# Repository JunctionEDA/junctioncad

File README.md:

<h1 align="center">Junction</h1>

<p align="center"><b>Real-time collaborative KiCad.</b><br>
Schematic and PCB editors where everyone works on the same design at once, on the desktop or in the browser,<br>
with any AI model as a teammate. Open source under GPL-3.0.</p>

<p align="center">
  <a href="https://junctioneda.com"><b>Open in the browser</b></a> ·
  <a href="https://github.com/JunctionEDA/junction/releases/latest"><b>Download for macOS, Windows, Linux</b></a> ·
  <a href="#design-with-an-ai"><b>Connect an AI</b></a>
</p>

<p align="center">

</p>

<!-- The demo video. GitHub plays a video inline only from a github.com/user-attachments URL: to get the inline
     player, drag docs/media/junction-demo.mp4 into this file in GitHub's editor and let the URL it inserts replace
     the poster link below. -->

https://github.com/user-attachments/assets/4089e936-c17c-4153-b253-e5f6324e9056

<p align="center"><sub>Four people build a Raspberry Pi Pico board together, from the first symbol to the filled planes. Music: Grieg, <i>In the Hall of the Mountain King</i>, Musopen (public domain).</sub></p>

## Install

| You want | Do this |
|---|---|
| The browser editor | Open [junctioneda.com](https://junctioneda.com) and sign in with GitHub. Nothing to install. |
| The desktop app | Download Junction for [macOS](https://junctioneda.com/download/macos), [Windows](https://junctioneda.com/download/windows) or [Linux](https://junctioneda.com/download/linux) (newest release; all files on the [releases page](https://github.com/JunctionEDA/junction/releases/latest)). |
| An AI app that designs with you | Add `https://junctioneda.com/mcp` as an MCP server (commands [below](#design-with-an-ai)). |
| Your own server | `cargo run` in [`server/`](server/README.md#running) with a Postgres database. |

Projects are ordinary KiCad files, and projects from any KiCad version from 6 to 10 open as they are. Everyone in a project should be on 2.0: it is built on a much newer KiCad than
1.0.9 and can write things an older client cannot read.

## Quick start

1. In the desktop app choose **File → Online Projects…**, or open the site, and sign in with GitHub.
2. Upload a KiCad project, or start a blank one.
3. **Share…** it with a GitHub username or an email address, or copy an edit, comment-only or view-only link.
4. Open the same schematic or board on both sides. Cursors and edits are live from there.

## What it does

<table>
<tr>
<td width="50%"><br><b>Live, together.</b> Everyone in the same schematic or board, each with their own view. Cursors, selections, drags in progress and edits arrive as they happen, between the desktop app and the browser alike.</td>
<td width="50%"><br><b>The whole board flow.</b> Update PCB from Schematic, placement, interactive routing, zones, DRC and the autorouter, following KiCad's own tools and dialogs.</td>
</tr>
<tr>
<td width="50%"><br><b>Any AI as a teammate.</b> An MCP server lets Claude, ChatGPT, Gemini, Cursor or a local model read and edit your projects. It points at what it means and proposes changes you accept or reject.</td>
<td width="50%"><br><b>GitHub sync.</b> Connect a project to a repository: push, pull and an item-level merge, through a GitHub App installed per repository.</td>
</tr>
<tr>
<td width="50%"><br><b>SPICE in the tab.</b> The simulator runs in the browser, on the schematic you are drawing.</td>
<td width="50%"><br><b>3D and fabrication.</b> The 3D viewer with real part models, and Gerbers, drill, placement and BOM with presets for JLCPCB and PCBWay.</td>
</tr>
</table>

And the rest of what a team needs:

- **Version history.** Every edit of the last 30 days can be scrubbed through; named versions and branches are kept
  for good, and two versions can be compared side by side.
- **Sharing and roles.** Editors, commenters and viewers, by GitHub username, email or link. View links open without
  an account.
- **Review.** Comment threads pinned to parts and nets that follow them when they move.
- **Offline.** The desktop app keeps working without a connection and merges when it returns.
- **Parts.** Search LCSC, Mouser and DigiKey and place the symbol and footprint straight into the schematic.
- **Plugins.** One catalog for built-in, KiCad and community plugins, sandboxed and permissioned.

## Design with an AI

Junction's server is an MCP endpoint. The model is your AI app's: Junction never calls one.

```sh
# Claude Code
claude mcp add --transport http junction https://junctioneda.com/mcp
```

```json
{ "mcpServers": { "junction": { "url": "https://junctioneda.com/mcp" } } }
```

claude.ai, ChatGPT, VS Code, Gemini CLI and Codex are on the site's **Connect an AI assistant** page and in
[server/README.md](server/README.md#mcp-server-any-ai-model-or-service). You sign in once and choose whether it may
make changes; the project's roles apply to it as they do to a person.

Then ask for a board. The model works through a Python harness (`run_python`): one tool call places parts by
name, wires them like the datasheet's application circuit, lays out and routes the board, and returns only what the
script prints, so a design costs few tokens. The Pico board in the video was drawn by
[two such scripts](server/scripts/demo-video/pico) before it was taken apart and put back together on camera.

## Status

Junction 2.2.1 is the current release (the name changed from KiCad Collaborative at 2.0.0). What to know:

- **It is a fork.** Collaboration is built into the editors, so you run Junction's build, not a plugin for stock
  KiCad. It follows upstream KiCad master (merged through 2026-11-17); About says "based on KiCad 10".
- **Same text field, same instant: the later value wins.** There is no merge inside one property. Undo restores
  your version of an item even if a collaborator changed it since.
- **All three desktop builds come from CI**, and each release run installs and launches them on clean machines
  before publishing. Windows and Linux have had less hands-on use than macOS.
- **The browser editor follows KiCad closely, not perfectly.** Small differences in behaviour are still being found
  and fixed.
- **AI-made boards need review.** The harness runs ERC, DRC and a design checklist, but nobody has ordered and
  powered the board in the video.
- **Vendor part search needs API keys** (Mouser, DigiKey) on a self-hosted server.

[COLLABORATION.md](COLLABORATION.md) lists what synchronizes and how conflicts resolve.

## How the demo video was made

Every shot is the real application against a local Junction server, staged by scripts in
[server/scripts/demo-video](server/scripts/demo-video):

- The Pico board was designed first by the [harness scripts](server/scripts/demo-video/pico); `prepare.mjs` then
  took every part, wire and track out of it and kept them.
- `record-junction.mjs` opens four browsers, one per person, and puts the design back one item at a time, each
  through that person's own editor with their mouse on it. Ada's window is the one filmed: the other cursors and
  their edits arriving are Junction's live sync doing its normal work.
- The AI's part is a real MCP call (highlight, then a proposal Ada accepts). The chat bubble is drawn by the video.
- `render.mjs` lays the footage on the music's bars, so each feature fills whole bars and some stretches play faster
  than they were recorded. The mouse pointer is drawn by the page, because a headless browser has none.

## Docs

[Roadmap](docs/ROADMAP.md) · [Architecture](docs/ARCHITECTURE.md) · [Collaboration guide](COLLABORATION.md) · [Server, protocol and self-hosting](server/README.md) ·
[MCP server](server/README.md#mcp-server-any-ai-model-or-service) ·
[Python harness](server/README.md#the-python-harness) · [Autorouter](server/README.md#board-autorouter) ·
[Changelog](CHANGELOG.md)

## License

[GPLv3](LICENSE), as KiCad. Junction is an independent fork and is not affiliated with or endorsed by the KiCad
project.

---

## Based on KiCad

Junction is built on [KiCad](https://kicad.org/) and stays current with it: every week
[upstream-sync](tools/upstream-sync/README.md) merges KiCad's latest changes, builds and tests them on Linux,
Windows and macOS, and only then moves `master`. For building the desktop code and its style, see KiCad's
[developer documentation](https://dev-docs.kicad.org). Problems with Junction belong in this repository's
issues, not KiCad's tracker.

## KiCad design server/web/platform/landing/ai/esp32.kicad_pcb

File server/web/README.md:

# server/web: the browser app

TypeScript and React, bundled by esbuild into `server/static` (`npm run build`; the entry points are in
`server/package.json`). The tree has three areas:

```
web/
  main.tsx            the React chrome's entry (static/dist/ui.js)
  shared/             used by every area: the store contract, theme, keys, units, menus, the UI kit, styles
    components/       menu bar, toolbars, docks, panes, selects, dialogs' widgets
    styles/           the Tailwind entry and home.css
    itemdoc/          JSON item documents (.jpart, .jasm): the format, item changes, the live session
    viewport3d/       the 3D viewport the modelling domains draw in
  platform/           what every kind of project shares
    home/             projects list, upload, sharing (ShareDialog), time page
    landing/          the public home page and its demos
    onboarding/       first-run guide
    github/           GitHub sync
    review/           version compare and review (a domain's own documents through a renderer it registers)
    history/          versions, branches and merging for the editor of any document that is not KiCad's
    mcp/              what a domain hands the headless tool host so an AI assistant can work on its documents
    wakatime/         time tracking
    documents/        how the shell hands a document to a domain's own editor
    doctabs/          the shell of an open project: its tab bar, what an element and a PCB are, the project's own document
    projecthome/      the Home tab: the file tree, create, import, who is where
    admin/, styleguide/
  domains/            one folder per kind of design work
    registry.ts       what each domain is, which files it opens and which domains it reads
    mcp-tools.ts      the domains that bring AI tools of their own (each from its mcp/ folder)
    pcb/              electronics: schematic, symbols, board, footprints, fab, simulation (shipped)
    mechanical/       part studios: sketcher, features, history tree, boards in and out, on OpenCascade (CONTRACT.md)
    assembly/         assemblies: instances of parts and boards, mates and their solver, interference, BOM
    physics/  silicon/  robotics/  manufacturing/   (planned)
```

Rules of thumb:

- `shared/` and `platform/` should not grow new imports from `domains/`. Some imports already go that way (the
  chrome mounts the electronics editor's menus and toolbars, and `platform/review` diffs KiCad documents). Untangling
  them is on the roadmap. Don't add more.
- A domain may import from `shared/` and `platform/`, but never from another domain's internals. Share through
  `shared/` or the domain's documented exports instead.
- Files under `domains/pcb/generated/` are written by `server/scripts/gen_*.py` from the C++ sources. Don't edit
  them by hand.
- `domains/mechanical/generated/` and `domains/assembly/generated/` are written by
  `scripts/gen-cad-registry.mjs` (`npm run gen:cad`, which `check`, `build` and the tests run) from the files in
  those domains' `features/`, `tools/`, `panels/`, `services/` and `mates/` folders. They are not committed.
- A project is a Home tab and any number of elements, one tab each: PCBs, part studios, assemblies
  (`platform/doctabs`, `platform/projecthome`). `domains/registry.ts` says which document kinds exist and which
  bundle draws each; a domain's editor registers itself through `platform/documents/host.ts`.
- A PCB is a KiCad project in a folder of its own, and the schematic and board editor sees one PCB at a time:
  `project.docs` is that PCB's documents with paths relative to its folder, `project.allDocs` is the whole
  project. Code outside the electronics editor reads `allDocs`. `platform/doctabs/pcbs.ts` has the rules; the
  section "Document tabs and the shell" of `domains/mechanical/CONTRACT.md` has the rest.

The tests in `server/static/tests` find modules with `webPath()` (`static/tests/web-path.js`), which knows
which area each top-level folder lives in.

See [STYLE.md](STYLE.md) for how the chrome is written, and [docs/ARCHITECTURE.md](../../docs/ARCHITECTURE.md)
for the whole repository.

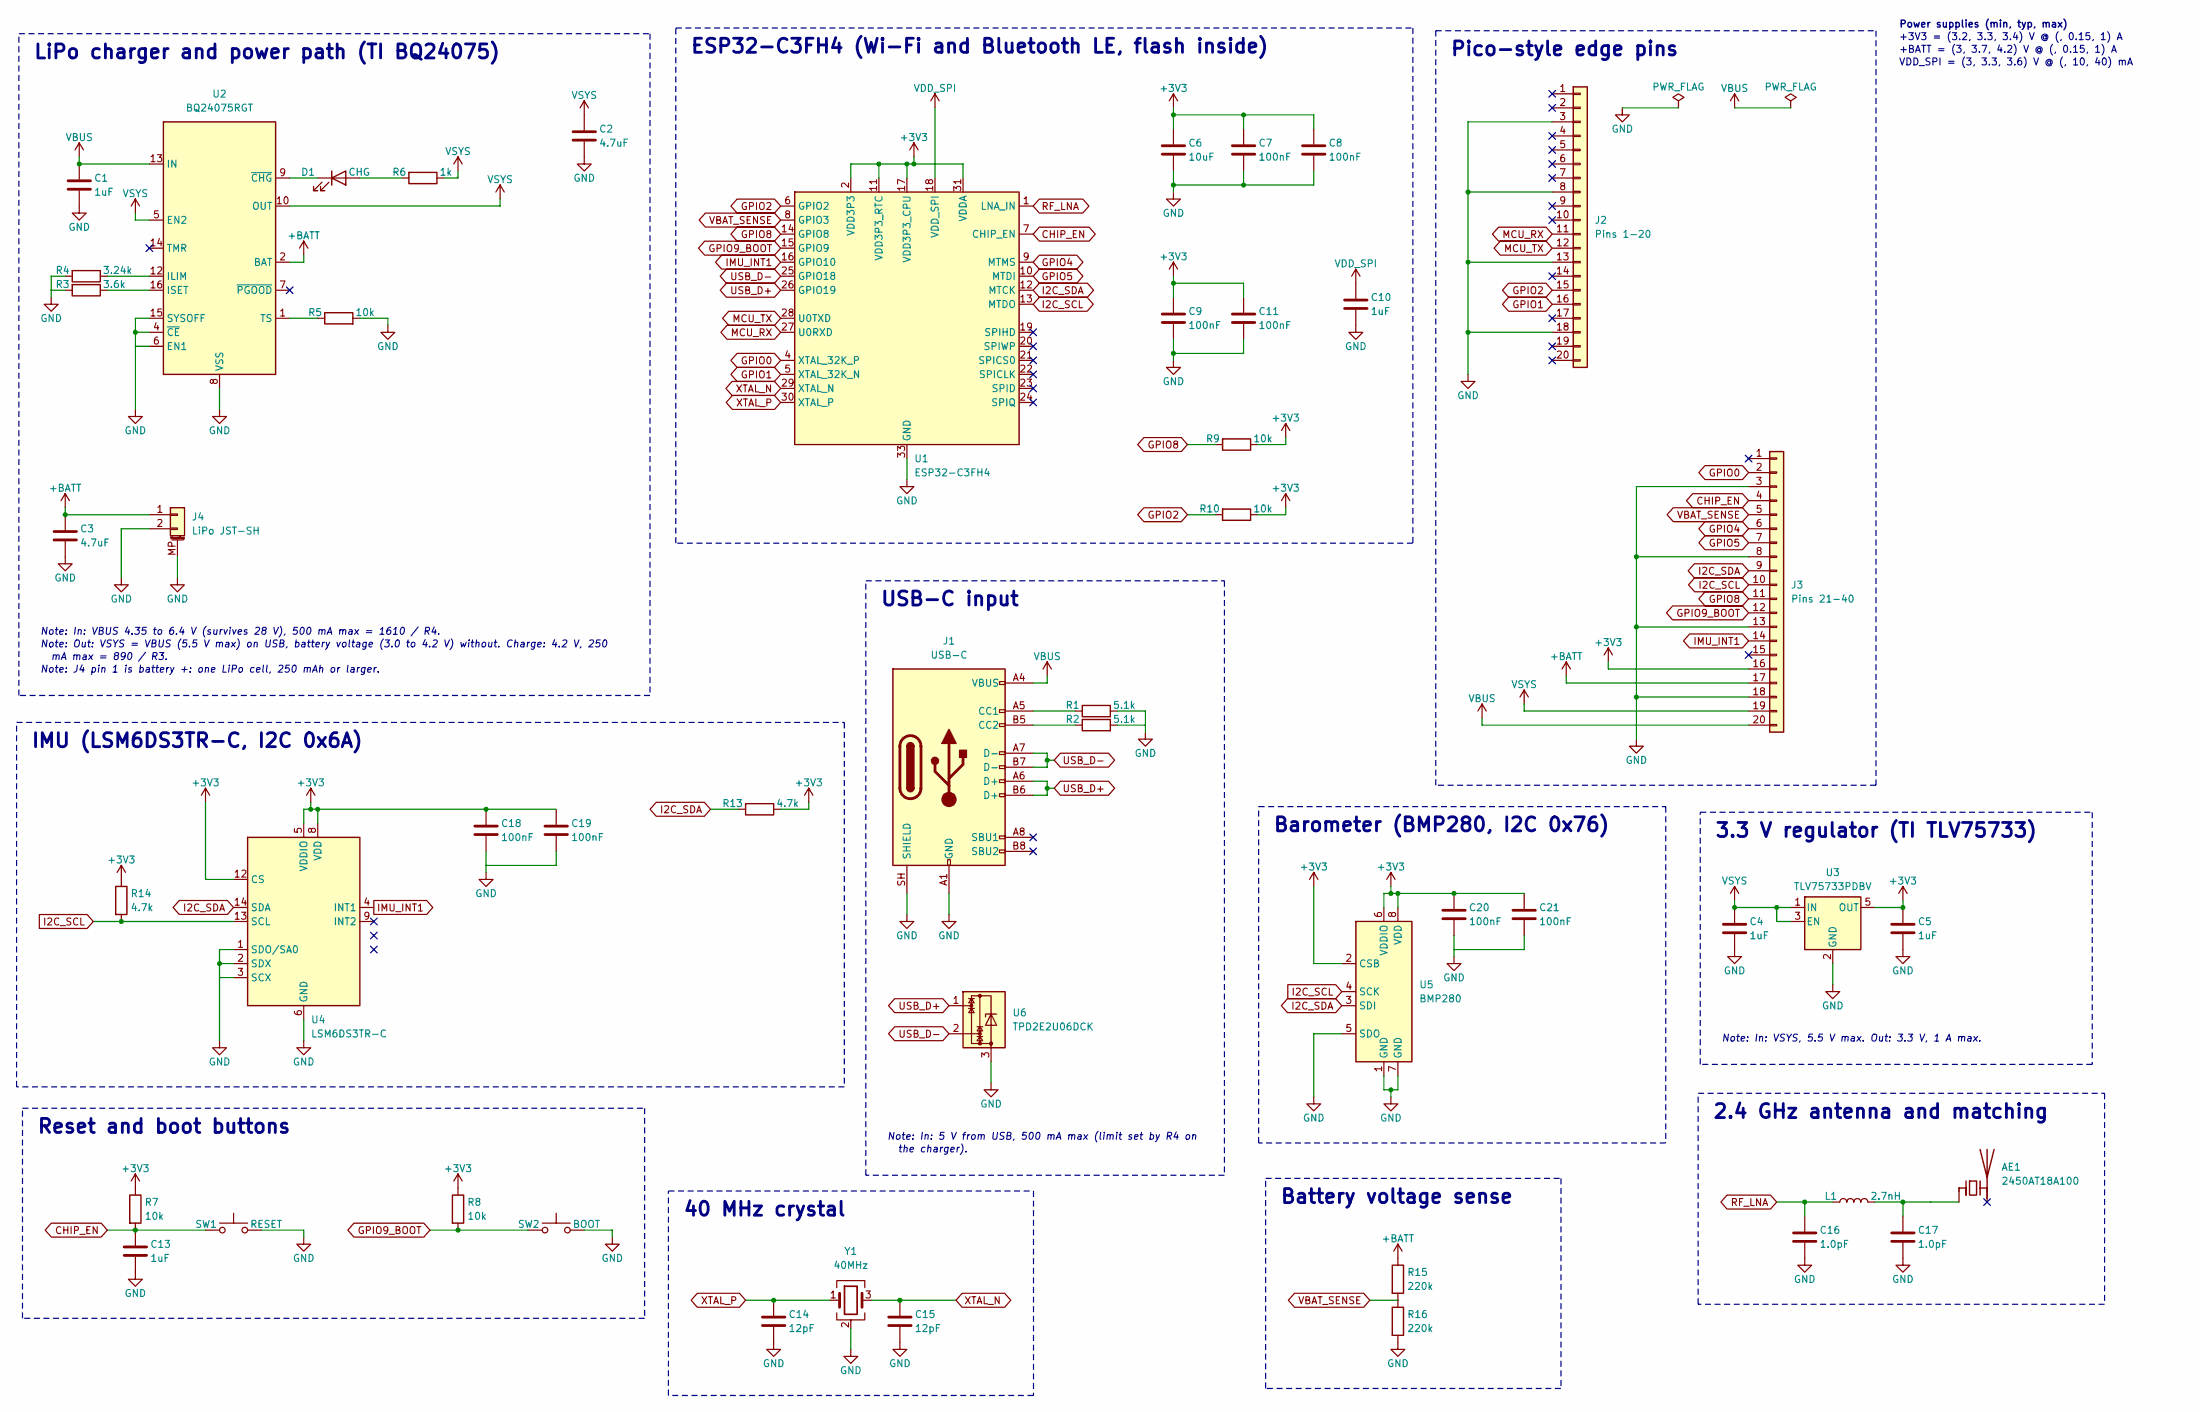
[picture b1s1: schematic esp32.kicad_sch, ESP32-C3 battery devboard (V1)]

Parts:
AE1: 2450AT18A100; Johanson_2450AT18x100; MPN 2450AT18A100E
C1, C4, C5, C10, C13: 1uF; C_0402_1005Metric; Voltage 25V; MPN CL05A105KA5NQNC
C2, C3: 4.7uF; C_0603_1608Metric; Voltage 16V; MPN CL10A475KO8NNNC
C6: 10uF; C_0603_1608Metric; Voltage 10V; MPN CL10A106KP8NNNC
C7, C8, C9, C11, C18, C19, C20, C21: 100nF; C_0402_1005Metric; Voltage 16V; MPN CL05B104KO5NNNC
C14, C15: 12pF; C_0402_1005Metric; Voltage 50V; MPN CL05C120JB5NNNC
C16, C17: 1.0pF; C_0402_1005Metric; Voltage 50V; MPN CL05C010CB5NNNC
D1: CHG; LED_0402_1005Metric; MPN LTST-C281KGKT
J1: USB-C; USB_C_Receptacle_GCT_USB4105-xx-A_16P_TopMnt_Horizontal; MPN USB4105-GF-A
J2: Pins 1-20; PinHeader_1x20_P2.54mm_Vertical; MPN 61302011121
J3: Pins 21-40; PinHeader_1x20_P2.54mm_Vertical; MPN 61302011121
J4: LiPo JST-SH; JST_SH_BM02B-SRSS-TB_1x02-1MP_P1.00mm_Vertical; MPN BM02B-SRSS-TB
L1: 2.7nH; L_0402_1005Metric; MPN LQG15HS2N7S02D
R1, R2: 5.1k; R_0402_1005Metric; MPN RC0402FR-075K1L
R3: 3.6k; R_0402_1005Metric; MPN RC0402FR-073K6L
R4: 3.24k; R_0402_1005Metric; MPN RC0402FR-073K24L
R5, R7, R8, R9, R10: 10k; R_0402_1005Metric; MPN RC0402FR-0710KL
R6: 1k; R_0402_1005Metric; MPN RC0402FR-071KL
R13, R14: 4.7k; R_0402_1005Metric; MPN RC0402FR-074K7L
R15, R16: 220k; R_0402_1005Metric; MPN RC0402FR-07220KL
SW1: RESET; SW_Push_SPST_NO_Alps_SKRK; MPN SKRKAEE020
SW2: BOOT; SW_Push_SPST_NO_Alps_SKRK; MPN SKRKAEE020
U1: ESP32-C3FH4; QFN-32-1EP_5x5mm_P0.5mm_EP3.7x3.7mm; MPN ESP32-C3FH4
U2: BQ24075RGT; QFN-16-1EP_3x3mm_P0.5mm_EP1.7x1.7mm; MPN BQ24075RGTR
U3: TLV75733PDBV; SOT-23-5; MPN TLV75733PDBVR
U4: LSM6DS3TR-C; LGA-14_3x2.5mm_P0.5mm_LayoutBorder3x4y; MPN LSM6DS3TR-C
U5: BMP280; Bosch_LGA-8_2x2.5mm_P0.65mm_ClockwisePinNumbering; MPN BMP280
U6: TPD2E2U06DCK; SOT-323_SC-70; MPN TPD2E2U06DCKR
Y1: 40MHz; Crystal_SMD_2016-4Pin_2.0x1.6mm; MPN NX2016SA-40M-EXS00A-CS06465

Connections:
+3V3: C5.1, C6.1, C7.1, C8.1, C9.1, C11.1, C18.1, C19.1, C20.1, C21.1, J3.16, R7.1, R8.1, R9.1, R10.1, R13.1, R14.1, U1.2 (VDD3P3), U1.3 (VDD3P3), U1.11 (VDD3P3_RTC), U1.17 (VDD3P3_CPU), U1.31 (VDDA), U1.32 (VDDA), U3.5 (OUT), U4.5 (VDDIO), U4.8 (VDD), U4.12 (CS), U5.2 (CSB), U5.6 (VDDIO), U5.8 (VDD)
+BATT: C3.1, J3.17, J4.1, R15.1, U2.2 (BAT), U2.3 (BAT)
CHIP_EN: C13.1, J3.4, R7.2, SW1.1, U1.7 (CHIP_EN)
GND: C1.2, C2.2, C3.2, C4.2, C5.2, C6.2, C7.2, C8.2, C9.2, C10.2, C11.2, C13.2, C14.2, C15.2, C16.2, C17.2, C18.2, C19.2, C20.2, C21.2, J1.A1 (GND), J1.A12 (GND), J1.B1 (GND), J1.B12 (GND), J1.SH (SHIELD), J2.3, J2.8, J2.13, J2.18, J3.3, J3.8, J3.13, J3.18, J4.2, J4.MP (MountPin), R1.2, R2.2, R3.2, R4.2, R5.2, R16.2, SW1.2, SW2.2, U1.33 (GND), U2.4 (~CE), U2.6 (EN1), U2.8 (VSS), U2.15 (SYSOFF), U2.17 (VSS), U3.2 (GND), U4.1 (SDO/SA0), U4.2 (SDX), U4.3 (SCX), U4.6 (GND), U4.7 (GND), U5.1 (GND), U5.5 (SDO), U5.7 (GND), U6.3, Y1.2 (G), Y1.4 (G)
GPIO0: J3.2, U1.4 (XTAL_32K_P)
GPIO1: J2.16, U1.5 (XTAL_32K_N)
GPIO2: J2.15, R10.2, U1.6 (GPIO2)
GPIO4: J3.6, U1.9 (MTMS)
GPIO5: J3.7, U1.10 (MTDI)
GPIO8: J3.11, R9.2, U1.14 (GPIO8)
GPIO9_BOOT: J3.12, R8.2, SW2.1, U1.15 (GPIO9)
I2C_SCL: J3.10, R14.2, U1.13 (MTDO), U4.13 (SCL), U5.4 (SCK)
I2C_SDA: J3.9, R13.2, U1.12 (MTCK), U4.14 (SDA), U5.3 (SDI)
IMU_INT1: J3.14, U1.16 (GPIO10), U4.4 (INT1)
MCU_RX: J2.11, U1.27 (U0RXD)
MCU_TX: J2.12, U1.28 (U0TXD)
unnamed: AE1.1 (FEED), C17.1, L1.2
unnamed: D1.2 (A), R6.2
unnamed: D1.1 (K), U2.9 (~CHG)
unnamed: J1.A5 (CC1), R1.1
unnamed: J1.B5 (CC2), R2.1
unnamed: R4.1, U2.12 (ILIM)
unnamed: R3.1, U2.16 (ISET)
unnamed: R5.1, U2.1 (TS)
RF_LNA: C16.1, L1.1, U1.1 (LNA_IN)
USB_D+: J1.A6 (D+), J1.B6 (D+), U1.26 (GPIO19), U6.1
USB_D-: J1.A7 (D-), J1.B7 (D-), U1.25 (GPIO18), U6.2
VBAT_SENSE: J3.5, R15.2, R16.1, U1.8 (GPIO3)
VBUS: C1.1, J1.A4 (VBUS), J1.A9 (VBUS), J1.B4 (VBUS), J1.B9 (VBUS), J3.20, U2.13 (IN)
VDD_SPI: C10.1, U1.18 (VDD_SPI)
VSYS: C2.1, C4.1, J3.19, R6.1, U2.5 (EN2), U2.10 (OUT), U2.11 (OUT), U3.1 (IN), U3.3 (EN)
XTAL_N: C15.1, U1.29 (XTAL_N), Y1.3
XTAL_P: C14.1, U1.30 (XTAL_P), Y1.1

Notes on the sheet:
LiPo charger and power path (TI BQ24075)
Note: In: VBUS 4.35 to 6.4 V (survives 28 V), 500 mA max = 1610 / R4.
Note: Out: VSYS = VBUS (5.5 V max) on USB, battery voltage (3.0 to 4.2 V) without. Charge: 4.2 V, 250
mA max = 890 / R3.
Note: J4 pin 1 is battery +: one LiPo cell, 250 mAh or larger.
ESP32-C3FH4 (Wi-Fi and Bluetooth LE, flash inside)
Pico-style edge pins
IMU (LSM6DS3TR-C, I2C 0x6A)
USB-C input
Note: In: 5 V from USB, 500 mA max (limit set by R4 on
the charger).
Barometer (BMP280, I2C 0x76)
Reset and boot buttons
3.3 V regulator (TI TLV75733)
Note: In: VSYS, 5.5 V max. Out: 3.3 V, 1 A max.
2.4 GHz antenna and matching
40 MHz crystal
Battery voltage sense
Power supplies (min, typ, max)
+3V3 = (3.2, 3.3, 3.4) V @ (, 0.15, 1) A
+BATT = (3, 3.7, 4.2) V @ (, 0.15, 1) A
VDD_SPI = (3, 3.3, 3.6) V @ (, 10, 40) mA

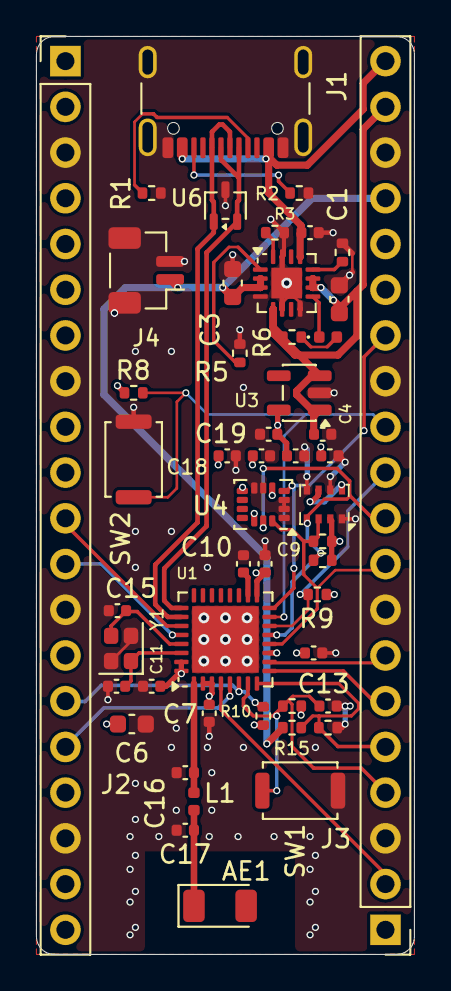
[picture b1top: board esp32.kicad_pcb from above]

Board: 4 copper layers, 21.0 x 51.0 mm, 50 parts (0 on the bottom side), 33 nets.

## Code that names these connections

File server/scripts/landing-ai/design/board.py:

# Board for the ESP32-C3 battery devboard (V1): Raspberry Pi Pico outline (21 x 51 mm), four layers, USB at the top, antenna at the bottom.
X0, Y0, W, H = 100, 50, 21, 51
FLOOR = {
    "J1": (10.5, 2.5, 180), "U6": (10.5, 9.4, 90), "R1": (6.4, 8.7, 0), "R2": (14.6, 8.7, 0),
    "J4": (6.1, 13.0, 90),
    "U2": (13.9, 13.7, 0), "R5": (11.3, 17.6, 90), "R3": (13.25, 10.9, 0), "C1": (15.2, 10.9, 0), "C3": (10.9, 13.7, 90),
    "R4": (17.0, 12.0, 90), "C2": (16.83, 14.6, 90), "D1": (16.2, 16.7, 0), "R6": (14.2, 16.7, 0),
    "U3": (14.6, 19.8, 180), "C4": (15.9, 22.1, 0), "C5": (12.9, 22.1, 180),
    "C18": (10.6, 23.3, 0), "C19": (12.5, 23.3, 0), "C20": (14.4, 23.3, 0), "C21": (16.3, 23.3, 0),
    "U4": (12.6, 26.0, 180), "U5": (16.0, 26.0, 180), "R13": (15.9, 28.05, 180), "R14": (15.9, 29.1, 180),
    "R8": (5.4, 19.8, 0), "SW2": (5.4, 23.5, 90),
    "U1": (10.5, 33.5, 90), "C9": (12.7, 29.3, 90), "C10": (11.5, 29.3, 90), "C8": (15.4, 34.25, 0), "R9": (15.6, 31.0, 180),
    "C7": (9.6, 37.6, 270), "C6": (5.3, 38.2, 0), "R10": (12.6, 37.75, 90),
    "Y1": (4.7, 34.0, 90), "C15": (4.5, 31.9, 180), "C14": (4.45, 36.1, 180), "C11": (6.4, 36.1, 180),
    "C16": (8.27, 40.9, 180), "L1": (8.75, 42.5, 270), "C17": (8.27, 44.1, 180), "AE1": (10.2, 48.3, 0),
    "R7": (14.2, 37.2, 180), "C13": (16.2, 37.2, 0), "R15": (14.2, 38.4, 0), "R16": (16.2, 38.4, 0), "SW1": (14.65, 41.9, 0),
}
board = project.board()
board.clear(outline=False)
print("sync", board.sync().get("added"))
board.outline(X0, Y0, X0 + W, Y0 + H)
board.rules(clearance=0.15, track_width=0.15, via_diameter=0.4, via_drill=0.25, min_track_width=0.15, min_clearance=0.15, edge_clearance=0.3, hole_clearance=0.15)
fixed = {r: (X0 + x, Y0 + y, rot) for r, (x, y, rot) in FLOOR.items()}
fixed["J2"] = (X0 + 1.61, Y0 + 1.37, 0)
fixed["J3"] = (X0 + 1.61 + 17.78, Y0 + 1.37 + 48.26, 180)
placed = board.autoplace(fixed=fixed, outline=(X0, Y0, X0 + W, Y0 + H))
print("placed", placed.get("score"), "clashes", board.clashes())
if len(board.info().get("copper_layers", [])) < 4:
    board.layers(4, planes=["In1.Cu", "In2.Cu"])
board.zone("GND", layer="In1.Cu", connect="solid")
board.zone("+3V3", layer="In2.Cu", connect="solid")
board.zone("GND", layer="B.Cu", connect="solid")
board.zone("GND", layer="F.Cu", connect="solid")
board.keepout((X0, Y0, X0 + 0.7, Y0 + H), tracks=True, vias=True, copper=False, name="left edge")
board.keepout((X0 + W - 0.7, Y0, X0 + W, Y0 + H), tracks=True, vias=True, copper=False, name="right edge")
board.stackup(fab="jlcpcb", layers=4)
board.rules(clearance=0.15, track_width=0.15, via_diameter=0.4, via_drill=0.25, min_track_width=0.15, min_clearance=0.15, edge_clearance=0.3, hole_clearance=0.15)
plan = board.plan(edge="bottom")
RFW = plan["route"]["widths"].get("RF_LNA", 0.35)
board.track("RF_LNA", ["U1.1", "C16.1", "L1.1"], width=RFW)
board.track(next(n for n, v in board.nets().items() if "AE1.1" in v["pads"]), ["L1.2", "C17.1", "AE1.1"], width=RFW)
board.track("GPIO8", ["U1.14", (114.2, 82.75), (115.09, 81.86), "R9.2"])
# USB pair, laid first as one coupled run (0.5 mm pitch): connector B6/B7 straight down through the ESD part's pads,
# down the lane between J4 and the charger, then round SW2 into U1's west pins. A6/A7 tie in: D+ under the connector, D- beside it.
UW = plan["route"]["widths"].get("USB_D+", 0.26)
board.track("USB_D+", ["J1.B6", (109.75, 59.1), (109.85, 59.2), "U6.1", (109.85, 60.9), (108.95, 61.8), (108.95, 77.0), (106.6, 79.35), (106.6, 81.557), (107.293, 82.25), "U1.26"], width=UW)
board.track("USB_D-", ["J1.B7", (111.25, 59.1), (111.15, 59.2), "U6.2", (111.15, 60.307), (109.45, 62.007), (109.45, 77.207), (107.1, 79.557), (107.1, 81.35), (107.5, 81.75), "U1.25"], width=UW)
board.track("USB_D+", ["J1.A6", (110.75, 55.3), (110.35, 54.9), (110.15, 54.9), (109.75, 55.3), "J1.B6"], width=UW)
board.track("USB_D-", ["J1.A7", (110.25, 56.85), (111.25, 57.85)], width=UW)
board.track("GND", ["U6.3", (110.5, 59.4)], width=0.2)
board.via("GND", (110.5, 59.4))
# the boot line crosses under the pair once, on the bottom layer, square to it
board.track("GPIO9_BOOT", ["R8.2", (108.3, 69.8)])
board.track("GPIO9_BOOT", ["SW2.1", (107.3, 75.6), (107.8, 75.1), (107.8, 70.3), (108.3, 69.8)])
board.via("GPIO9_BOOT", (108.3, 69.8))
board.track("GPIO9_BOOT", [(108.3, 69.8), (109.5, 71.0), (118.7, 71.0), "J3.12"], layer="B.Cu")
board.track("GPIO9_BOOT", ["U1.15", (113.75, 82.25)])
board.via("GPIO9_BOOT", (113.75, 82.25))
board.track("GPIO9_BOOT", [(113.75, 82.25), (113.75, 72.2), (114.95, 71.0)], layer="B.Cu")
print("antenna", board.antenna())
print("thermal vias", board.thermal_vias())
def ground_at(x, y):
    for dx, dy in ((0.75, 0), (0, 0.75), (0, -0.75), (0.75, 0.75), (0.75, -0.75), (-0.75, 0)):
        p = (X0 + x + dx, Y0 + y + dy)
        if board.fence([p, (p[0] + 0.01, p[1])], spacing=1.0, net="GND")["vias"]:
            board.track("GND", [(X0 + x, Y0 + y), p], width=0.2)
            return (round(dx, 2), round(dy, 2))
print("ground vias", {r: ground_at(*xy) for r, xy in {"C13": (16.68, 37.2), "C8": (15.88, 34.25), "C14": (3.97, 36.1), "U5.7": (16.325, 25.2), "U5.5": (15.025, 25.2), "U5.1": (16.975, 26.8)}.items()})
have = board.nets()
R = plan["route"]
order = [n for n in ["GPIO9_BOOT"] + R["order"] + ["I2C_SDA", "I2C_SCL", "IMU_INT1", "VBUS", "VSYS", "+BATT"] if n in have]
order = [n for n in dict.fromkeys(order) if n not in ("USB_D+", "USB_D-")]
widths = {**R["widths"], "VBUS": 0.4, "VSYS": 0.4, "+BATT": 0.4, "+3V3": 0.3, "VDD_SPI": 0.3}
# cluster first: each chip with the parts the plan seats at its pins is wired inside itself before anything runs
# between clusters; pads of one supply that stand together share a pour instead of a track
near = plan["place"].get("near", {})
def owner(ref, seen=()):
    o = near.get(ref)
    return ref if not o or o in seen else owner(o, (*seen, ref))
clusters = {}
for ref in near:
    clusters.setdefault(owner(ref), [owner(ref)]).append(ref)
print("power pours", board.power_pours())
r = board.route(order=order, widths=widths, kinds=R["kinds"], time_s=180, max_vias=2, groups=clusters or None)
print("routed", {k: r.get(k) for k in ("routed", "connections", "vias", "length_mm", "left")})
left = board.unrouted()
if left:
    print("retry", board.route(nets=list(left), widths=widths, kinds=R["kinds"], time_s=60, max_vias=2).get("left"))
left = [n for n in board.unrouted() if n != "GND"]
if left:
    print("retry 2", board.route(nets=left, widths=widths, time_s=60, max_vias=2, separate=False).get("left"))
import re
for _ in range(3):
    d = board.check(kind="unconnected_items", limit=10)
    lone = [m.groups() for m in (re.search(r"net 'GND'.*at \(([\d.]+), ([\d.]+)\)", t) for t in d["first"]) if m]
    if not lone:
        break
    print("lone ground pads", [(x, y, ground_at(float(x) - X0, float(y) - Y0)) for x, y in lone])
    board.fill()
print("finish", board.finish())
board.track("GND", ["U4.3", "U4.2"], width=0.2)      # the IMU's ground pads side by side: tied pad to pad, straight
board.fill()
if board.unrouted():
    print("last ground", board.route(nets=list(board.unrouted()), time_s=40, max_vias=4, separate=False).get("left"))
    board.fill()
board.rules(min_text_height=0.6)
print("silk", board.silkscreen(rev="V1"))
d = board.check(limit=20)
print("drc", d["errors"], d["warnings"], d["by_kind"], d["first"])
print("board", board.info())
rv = board.review()
print("review", rv["errors"], rv["warnings"], rv["findings"])
if d["errors"] or rv["errors"] or board.unrouted():
    raise RuntimeError("not clean: rolled back")
